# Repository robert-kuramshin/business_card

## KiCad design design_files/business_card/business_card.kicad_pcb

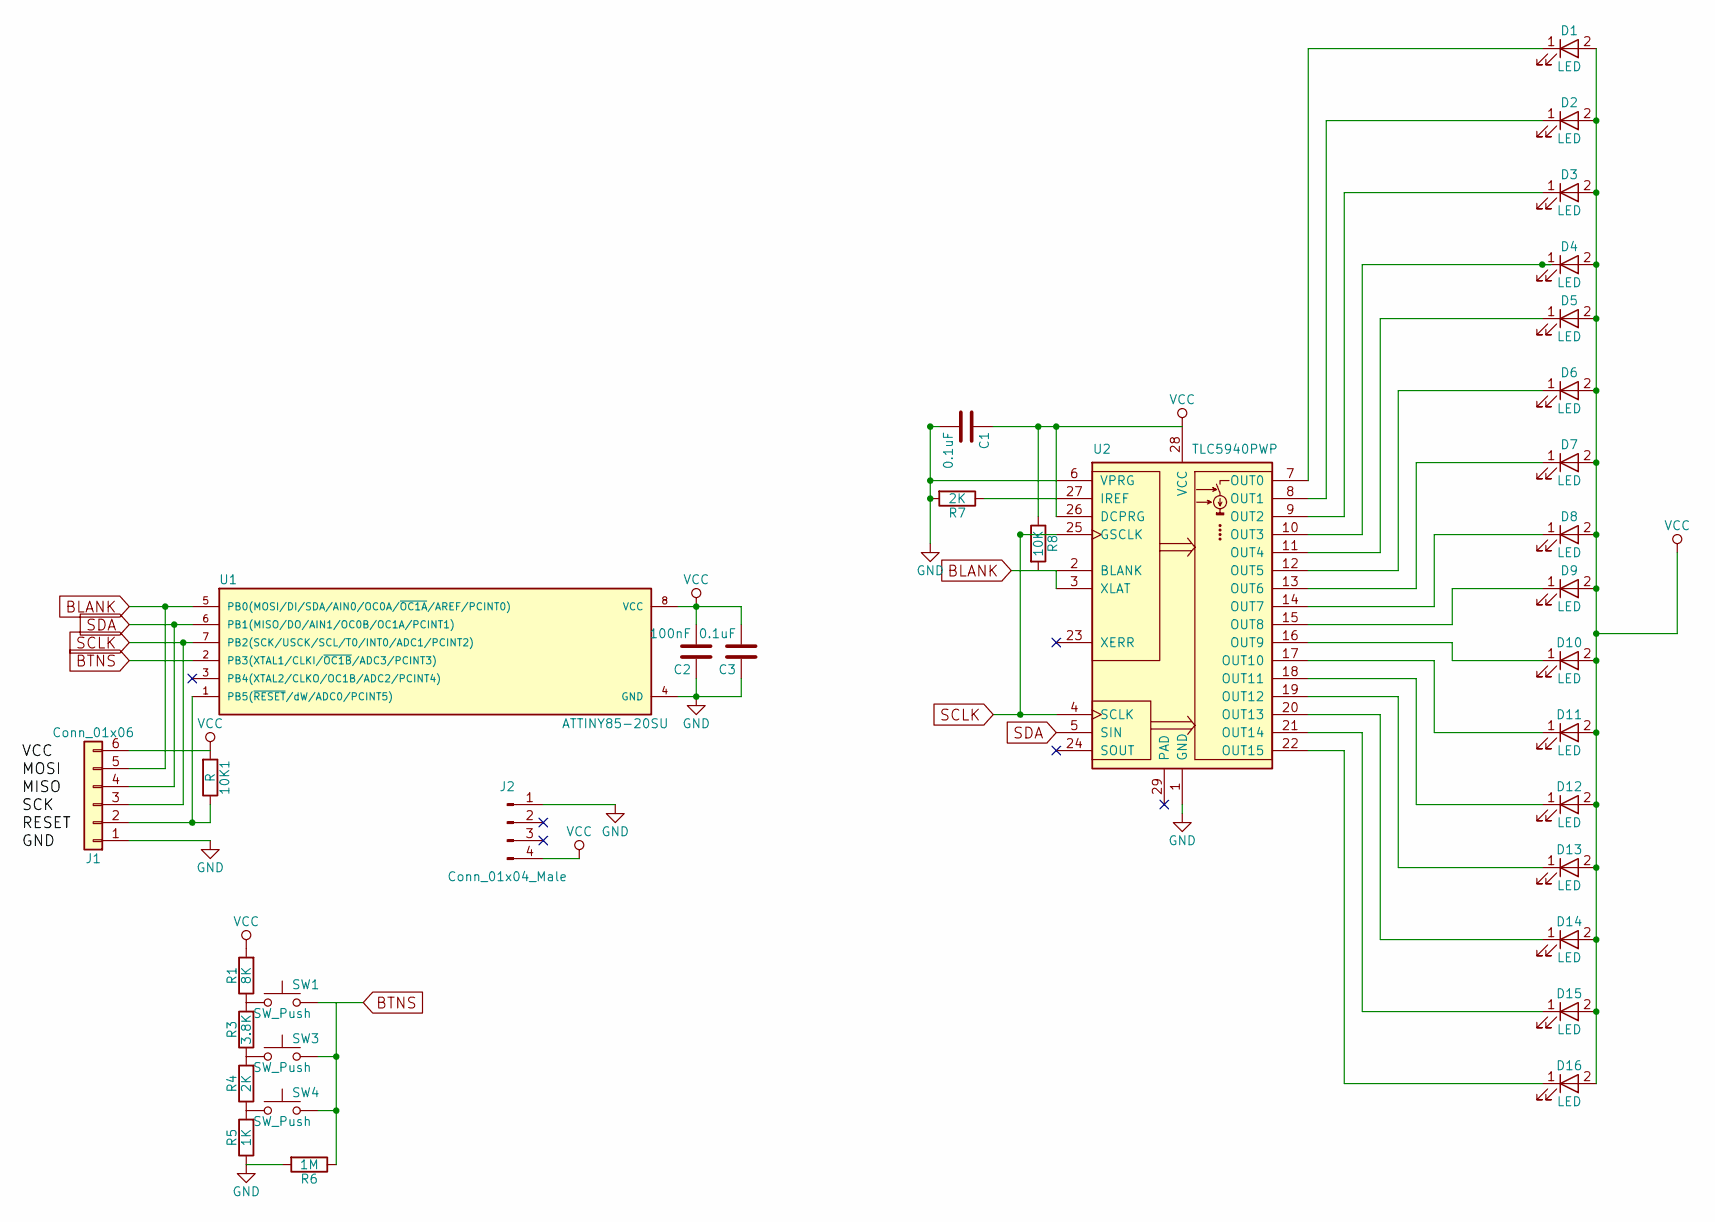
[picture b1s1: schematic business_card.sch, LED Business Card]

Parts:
10K1: R; R_0805
C1, C3: 0.1uF; C_0805
C2: 100nF; C_0805
D1, D2, D3, D4, D5, D6, D7, D8, D9, D10, D11, D12, D13, D14, D15, D16: LED; LED_0805
J1: Conn_01x06; pogo_connector
J2: Conn_01x04_Male; USB_connector
R1: 8K; R_0805
R3: 3.8K; R_0805
R4, R7: 2K; R_0805
R5: 1K; R_0805
R6: 1M; R_0805
R8: 10K; R_0805
SW1, SW3, SW4: SW_Push; SW_SPST_SKQG
U1: ATTINY85-20SU; SOIC-8_3.9x4.9mm_Pitch1.27mm
U2: TLC5940PWP; HTSSOP-28_4.4x9.7mm_Pitch0.65mm_ThermalPad

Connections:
BLANK: J1.5, U1.5 (PB0(MOSI/DI/SDA/AIN0/OC0A/~OC1A~/AREF/P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), U2.2 (BLANK), U2.3 (XLAT)
BTNS: SW1.2, U1.2 (PB3(XTAL1/CLKI/~OC1B~/ADC3/PCINT3))
GND: C1.2, C2.1, C3.1, J1.1, J2.1, R5.1, R6.2, R7.2, U1.4 (GND), U2.1 (GND), U2.6 (VPRG)
unnamed: 10K1.1, J1.2, U1.1 (PB5(~RESET~/dW/ADC0/PCINT5))
unnamed: D1.1 (K), U2.7 (OUT0)
unnamed: D2.1 (K), U2.8 (OUT1)
unnamed: D3.1 (K), U2.9 (OUT2)
unnamed: D4.1 (K), U2.10 (OUT3)
unnamed: D5.1 (K), U2.11 (OUT4)
unnamed: D6.1 (K), U2.12 (OUT5)
unnamed: D7.1 (K), U2.13 (OUT6)
unnamed: D8.1 (K), U2.14 (OUT7)
unnamed: D9.1 (K), U2.15 (OUT8)
unnamed: D10.1 (K), U2.16 (OUT9)
unnamed: D11.1 (K), U2.17 (OUT10)
unnamed: D12.1 (K), U2.18 (OUT11)
unnamed: D13.1 (K), U2.19 (OUT12)
unnamed: D14.1 (K), U2.20 (OUT13)
unnamed: D15.1 (K), U2.21 (OUT14)
unnamed: D16.1 (K), U2.22 (OUT15)
unnamed: R1.1, R3.2, SW1.1
unnamed: R3.1, R4.2, SW3.1
unnamed: R4.1, R5.2, SW4.1
unnamed: R6.1, SW3.2, SW4.2
unnamed: R7.1, U2.27 (IREF)
SCLK: J1.3, U1.7 (PB2(SCK/USCK/SCL/T0/INT0/ADC1/PCINT2)), U2.4 (SCLK), U2.25 (GSCLK)
SDA: J1.4, U1.6 (PB1(MISO/DO/AIN1/OC0B/OC1A/PCINT1)), U2.5 (SIN)
VCC: 10K1.2, C1.1, C2.2, C3.2, D1.2 (A), D2.2 (A), D3.2 (A), D4.2 (A), D5.2 (A), D6.2 (A), D7.2 (A), D8.2 (A), D9.2 (A), D10.2 (A), D11.2 (A), D12.2 (A), D13.2 (A), D14.2 (A), D15.2 (A), D16.2 (A), J1.6, J2.4, R1.2, R8.1, U1.8 (VCC), U2.26 (DCPRG), U2.28 (VCC)

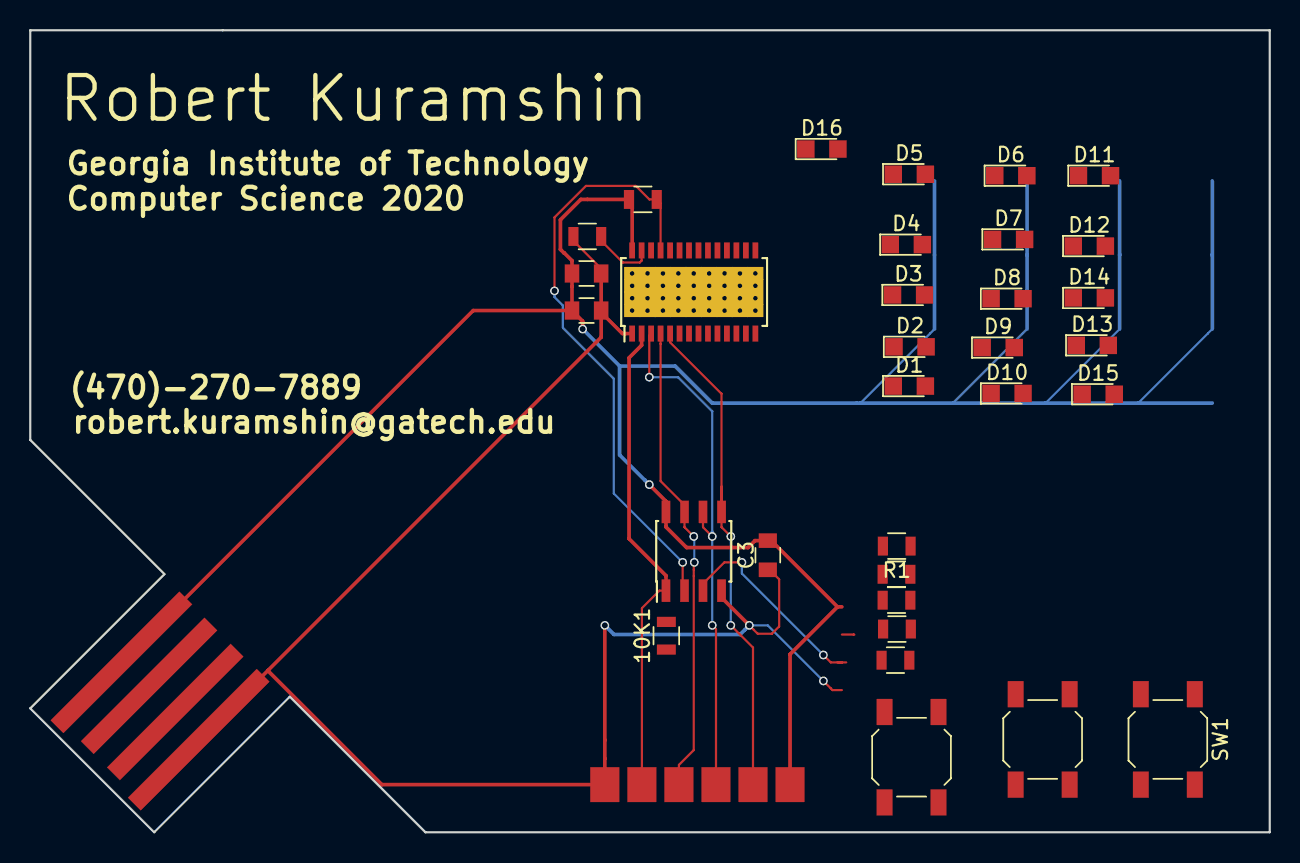
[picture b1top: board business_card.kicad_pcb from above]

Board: 2 copper layers, 85.0 x 55.0 mm, 34 parts (0 on the bottom side), 28 nets.

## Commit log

2017-09-24 design files for business card v1.0
2017-09-24 removed design files from other projects
2017-09-25 minor rerouting changes
2017-10-20 switching to 3 wire control
2017-10-20 2 buttons and 15 leds
2017-10-24 progress on configuring 15 leds
